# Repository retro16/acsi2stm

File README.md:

ACSI2STM: Atari ST hard drive emulator
======================================

This project is a hard drive emulator for your Atari ST using an inexpensive
STM32 microcontroller and a SD card.

The aim of this project is to be very easy to build, extremely cheap, reliable
and safe for your precious vintage machine. A lot of effort has been put in the
documentation, both for usage and technical aspects.

It can work in 3 ways:

* Mount standard SD/SDHC/SDXC cards on the Atari (FAT16/FAT32/ExFAT).
* Expose raw SD cards as ACSI hard disks connected to the Atari.
* Expose ACSI hard disk image files as hard disks connected to the Atari.

It can also work on STs with broken DMA chips by using the PIO firmware.

It also provides an UltraSatan compatible real-time clock if you add a simple
3V lithium battery such as a CR2032.

Legacy hardware based on Blue Pill designs are supported to various degrees.
[compatibility](doc/compatibility.md) explains which hardware is supported by
this version.

See [RELEASE NOTES](release_notes.md) for details about the current version.

**Final version:** Both software and hardware parts are considered finished, the
project is now mature. Feedback is still welcome and occasional bug fixes may be
released.

Documentation
-------------

The *doc* directory provides documentation for the end-user as well as hardware
implementors or curious people.

This is what you can find:

* [quick_start](doc/quick_start.md): How to setup and upgrade the unit.
* [tutorial](doc/tutorial.md): A tutorial about using hard drives on an Atari ST
  if you never used one before. It will help setting up various hardware
  combinations.
* [standard_configurations](doc/standard_configurations.md): Instructions to
  setup ACSI2STM depending on your hardware and what you want to achieve.
* [tools](doc/tools.md): Documentation for tools provided with ACSI2STM.
* [compatibility](doc/compatibility.md): Information about hardware, firmware
  and software compatibility.
* [troubleshooting](doc/troubleshooting.md): Having problems? Have a look
  here.
* [ordering](doc/ordering.md): A tutorial to order the hardware and flash the
  firmware.
* [gemdrive](doc/gemdrive.md): Technical details about GemDrive. How to mix
  GemDrive with ACSI. How to install GemDrive for EmuTOS.
* [jumpers](doc/jumpers.md): Documents the various jumpers available on the PCB.
* [firmware](doc/firmware.md): Describes the many firmware variants pre-built
  in the release package. Also provides a step-by-step tutorial to compile and
  customize firmware yourself.
* [hardware](doc/hardware.md): How to design and build an ACSI2STM unit
  from scratch (hand wired or your own PCB design).
* [protocols](doc/protocols.md): Technical details about the communication
  protocol between the ACSI2STM unit and the Atari ST.

To people buying/selling hardware
---------------------------------

There are people building and selling products based on this code. This project
is not directly related to any of these people, there is no official hardware
supplier.

Building and selling units is encouraged, as long as the spirit of free software
is preserved and the terms of the license are respected.

The code here is released under the GPLv3 license (see LICENSE file). This has
some implications:

* If you bought a product that contains code based on this project (modified or
  not), you can request the source code to the firmware contained in your
  product. The seller/maker of the product is legally required to provide it.
* If you sell any product based on this code, you **must** provide a link to
  the source.
* If you sell any product based on a modified version of this code, or reusing
  parts of this code, you **must** provide a link to the whole source code of
  the modified version with the product, including any additional
  features/modules you may have added.
* If you redistribute binary versions (modified or not), you **must** provide a
  link to the source code matching exactly the binary you redistribute.
* Any modified version must retain the GPLv3 or a compatible license.
* The name ACSI2STM is not protected. You can reuse it as you wish. Making a
  clear distinction between this code and your product will be greatly
  appreciated (most sellers do).
* The code is provided without warranty, so hardware troubleshooting is best
  effort. If you bought a unit and you have issues, you should contact the
  seller first. Anyway, constructive feedback (including bug reports) is always
  appreciated.
* If a seller refuses to provide the sources, please open a GitHub issue to let
  me know.

**Note**: the Mega STE PCB is copyrighted by Olivier Jan and is released under
the MIT license so it does not have the same restrictions.

If you sell ACSI2STM units, please consider selling the new compact PCB design
instead of custom designs. If the compact design isn't to your taste, please
open a GitHub issue and talk about possible improvements.

Credits
-------

I would like to thank the people that put invaluable information online that
made this project possible in a finite amount of time. Without them, this
project would have not existed. I would also like to thank people giving
feedback, contributing to make the project better.

* Bill Greiman for the SdFat library. It's really fantastic.
* The http://atari.8bitchip.info website and his author, who also contributes
  on various forums.
* The Hatari developpers. I used its source code as a reference for ACSI
  commands, as well as the excellent GEMDOS drive implementation.
* The people who made the FreeMiNT TOS documentation.
* The EmuTOS developers, again the source code is an excellent reference.
* The UltraSatan project for their documentation and their RTC clock tool.
* Uwe Seimet for his SCSI testing tool.
* Jean-Louis Guérin (DrCoolZic) for his excellent "Atari Hard Disk File Systems
  Reference Guide".
* mamejay, Ben Leggett, S0urceror, Sr Antonio, Edu Arana, Frederick321,
  Ulises74, Maciej G., Olivier Gossuin, Marcel Prisi and Tomasz Orczyk for
  their very detailed feedback that helped me a lot for fine tuning the DRQ/ACK
  signals and other various aspects of the projects.
* All people contributing on GitHub, for their code, their ideas, the issues
  they submit, and their patience when things fail !
* Olivier Jan for the Mega STE PCB.
* Tomasz Orczyk for finding a way to have a much better version of GCC and a lot
  of feedback.
* Joe Ceklosky for his feedback and help on fixing RTC issues.
* François Planque for his [extensive explanation about the Mega STE internal drive](https://www.fplanque.com/tech/retro/atari/atari-st-acsi2stm-mega-ste/)
* Diego Parrilla for making the PCB much more reliable.
* Christian Zietz for his expert insight on program loading and Alt-RAM.

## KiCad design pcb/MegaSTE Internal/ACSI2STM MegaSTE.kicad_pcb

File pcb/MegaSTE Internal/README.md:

# ACSI2STM-MSTE
 
This a KiCAD (6.0) design to host an [ACSI2STM](https://github.com/retro16/acsi2stm) directly inside an Atari Mega STE using the internal connector. 
The PCB has been designed to accomodate version 2.x and 3.x of ACSI2STM (aka V2) but also the old V1 design. 
- No external power is required, the 5v is taken directly from the internal ACSI connector, but this has only been tested with a fully recapped PSU. 
- A set of jumper needs to be soldered to configure the board for V1 or V2 as noted on the PCB.

## BOM
- 100 nF Capacitor
- 10uF Radial Capacitor
- Male 2.54 header (Optional)
- 1N5817 Diode 
- Female 2.54 headers
- Amphenol GSD090012SEU SD Card socket
- STM32F103C8T6 "Blue Pill" (original one is highly recommended!!!). 
- Firmware from [ACSI2STM](https://github.com/retro16/acsi2stm)

## Configuration
Configuration is done by simple solder bridges on the pads, instructions are also written on PCB.

### For V1:
- Solder bridge: JP1, JP2, JP3, JP4, JP5, JP6, JP7
- Solder bridge pads 1 and 2 of JP9 (2 leftmost pads)
- Solder bridge pads 1 and 2 of JP10 (2 leftmost pads)

### For V2: 
- Solder bridge pads 2 and 3 of JP9 (2 leftmost pads)
- Solder bridge pads 2 and 3 of JP10 (2 leftmost pads)

### For V3: 
- Solder bridge pads 2 and 3 of JP9 (2 leftmost pads)
- Solder bridge pads 2 and 3 of JP10 (2 leftmost pads)
- Solder bridge JP8 

### Firmware update

A male 3 pin header is optional and only required if you want to program the STM32 without removing it from the Atari.
The RX and TX marking correspond to the STM32 pins A10 an A09, to program the STM32 connect the board's RX to your USB-TTL TX and the board's TX to your USB-TTL-RX:
| USB-TTL | ACSI2STM |
|:---------:|:----------:|
| GND | GND |
| RX | TX |
| TX | RX |

In order to update the STM32:
1. Power-off your MegaSTE
2. Plug the GND, RX and TX to your USB-TTL adapter
3. Move BOOT0 jumper to "1" on the BluePill
3. Plug USB to ACSI2STM
4. Follow the normal update process.
5. Unplug USB, RX, TX and GND
6. Move BOOT0 jumper back to original position
7. Power-on the Mega STE

:warning: Although the diode should avoid USB power from flowing back to the Mega STE, I haven't tested USB plugged-in while the MegaSTE is powered on. :warning:

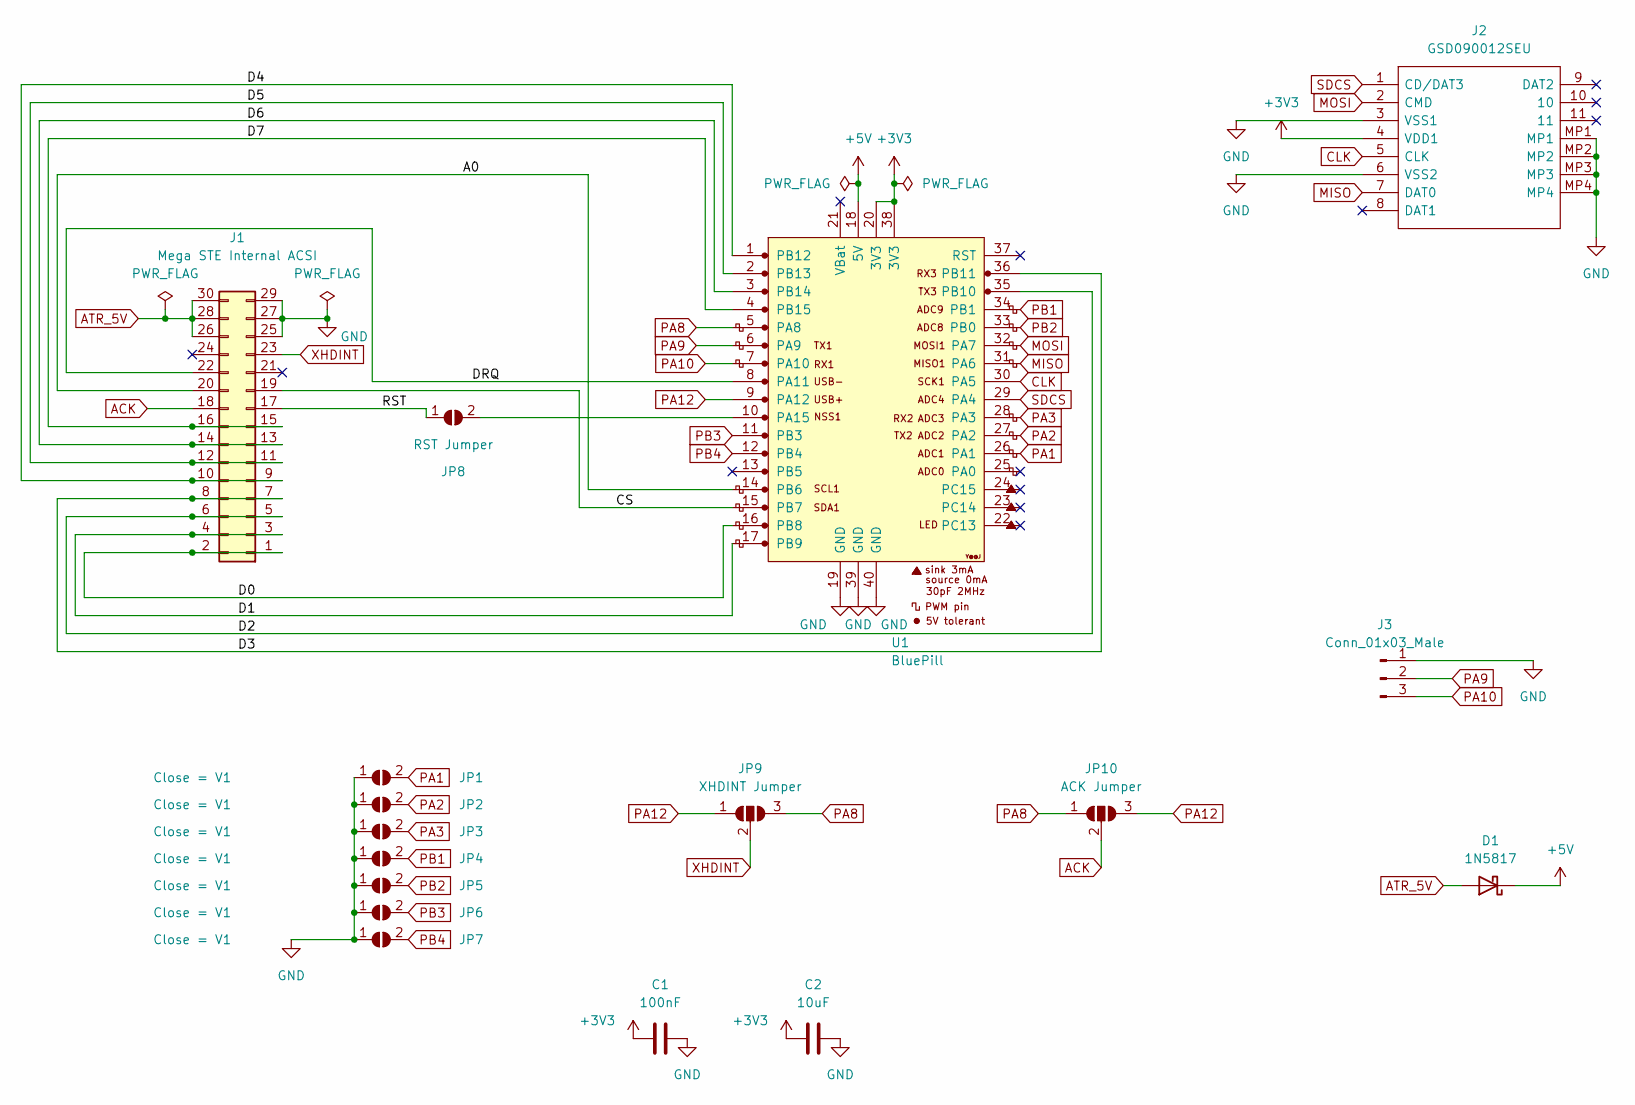
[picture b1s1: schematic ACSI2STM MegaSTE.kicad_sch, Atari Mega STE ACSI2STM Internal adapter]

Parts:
C1: 100nF; C_Disc_D4.3mm_W1.9mm_P5.00mm
C2: 10uF; C_Radial_D5.0mm_H5.0mm_P2.00mm
D1: 1N5817; D_DO-41_SOD81_P10.16mm_Horizontal
J1: Mega STE Internal ACSI; PinSocket_2x15_P2.54mm_Vertical
J2: GSD090012SEU; Mouser Part Number 523-GSD090012SEU
J3: Conn_01x03_Male; PinHeader_1x03_P2.54mm_Vertical
JP1, JP2, JP3, JP4, JP5, JP6, JP7: Close = V1; SolderJumper-2_P1.3mm_Open_Pad1.0x1.5mm
JP8: RST Jumper; SolderJumper-2_P1.3mm_Open_RoundedPad1.0x1.5mm
JP9: XHDINT Jumper; SolderJumper-3_P1.3mm_Open_RoundedPad1.0x1.5mm
JP10: ACK Jumper; SolderJumper-3_P1.3mm_Open_RoundedPad1.0x1.5mm
U1: BluePill; YAAJ_BluePill_1

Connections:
+3V3: C1.1, C2.1, J2.4 (VDD1), U1.20 (3V3), U1.38 (3V3)
+5V: D1.1 (K), U1.18 (5V)
/A0: J1.20, U1.14 (PB6)
/CS: J1.19, U1.15 (PB7)
/D0: J1.1, J1.2, U1.16 (PB8)
/D1: J1.3, J1.4, U1.17 (PB9)
/D2: J1.5, J1.6, U1.35 (PB10)
/D3: J1.7, J1.8, U1.36 (PB11)
/D4: J1.9, J1.10, U1.1 (PB12)
/D5: J1.11, J1.12, U1.2 (PB13)
/D6: J1.13, J1.14, U1.3 (PB14)
/D7: J1.15, J1.16, U1.4 (PB15)
/DRQ: J1.22, U1.8 (PA11)
/RST: J1.17, JP8.1 (A)
ACK: J1.18, JP10.2 (C)
ATR_5V: D1.2 (A), J1.26, J1.28, J1.30
CLK: J2.5 (CLK), U1.30 (PA5)
GND: C1.2, C2.2, J1.25, J1.27, J1.29, J2.3 (VSS1), J2.6 (VSS2), J2.MP1, J2.MP2, J2.MP3, J2.MP4, J3.1, JP1.1 (A), JP2.1 (A), JP3.1 (A), JP4.1 (A), JP5.1 (A), JP6.1 (A), JP7.1 (A), U1.19 (GND), U1.39 (GND), U1.40 (GND)
MISO: J2.7 (DAT0), U1.31 (PA6)
MOSI: J2.2 (CMD), U1.32 (PA7)
unnamed: JP8.2 (B), U1.10 (PA15)
PA1: JP1.2 (B), U1.26 (PA1)
PA2: JP2.2 (B), U1.27 (PA2)
PA3: JP3.2 (B), U1.28 (PA3)
PA8: JP9.3 (B), JP10.1 (A), U1.5 (PA8)
PA9: J3.2, U1.6 (PA9)
PA10: J3.3, U1.7 (PA10)
PA12: JP9.1 (A), JP10.3 (B), U1.9 (PA12)
PB1: JP4.2 (B), U1.34 (PB1)
PB2: JP5.2 (B), U1.33 (PB0)
PB3: JP6.2 (B), U1.11 (PB3)
PB4: JP7.2 (B), U1.12 (PB4)
SDCS: J2.1 (CD/DAT3), U1.29 (PA4)
XHDINT: J1.23, JP9.2 (C)

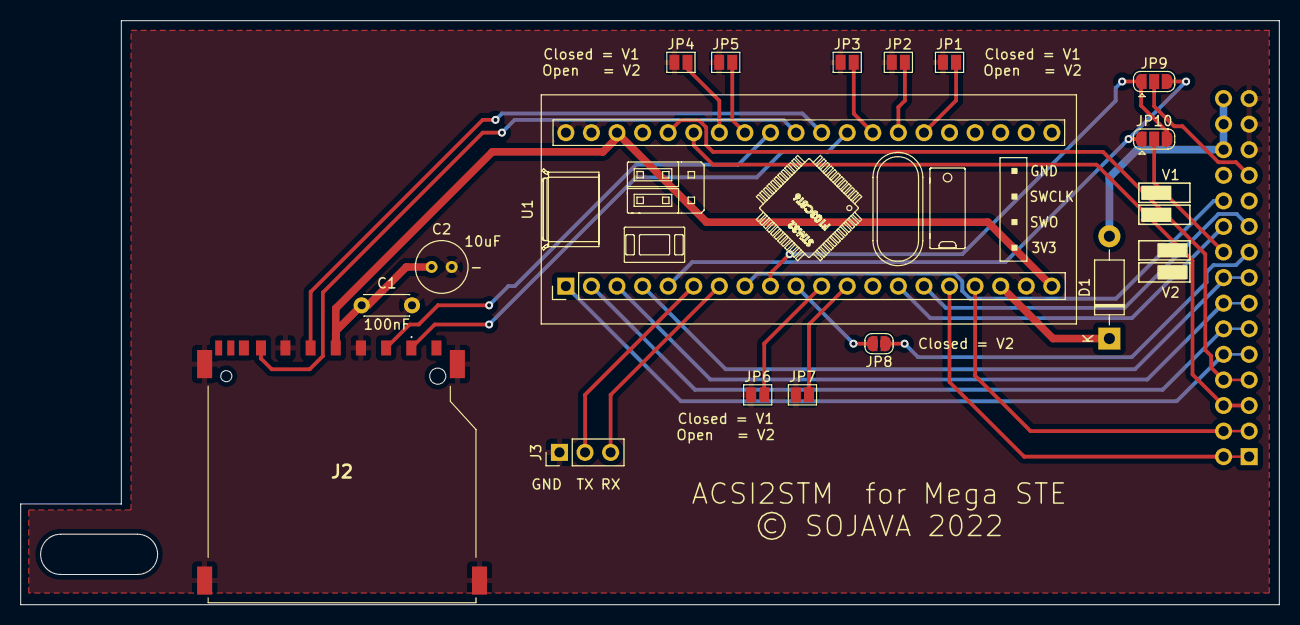
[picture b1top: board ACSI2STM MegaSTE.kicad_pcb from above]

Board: 2 copper layers, 125.0 x 58.0 mm, 17 parts (1 on the bottom side), 34 nets.

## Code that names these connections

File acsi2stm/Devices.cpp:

/* ACSI2STM Atari hard drive emulator
 * Copyright (C) 2019-2025 by Jean-Matthieu Coulon
 *
 * This program is free software: you can redistribute it and/or modify
 * it under the terms of the GNU General Public License as published by
 * the Free Software Foundation, either version 3 of the License, or
 * (at your option) any later version.
 *
 * This program is distributed in the hope that it will be useful,
 * but WITHOUT ANY WARRANTY; without even the implied warranty of
 * MERCHANTABILITY or FITNESS FOR A PARTICULAR PURPOSE.  See the
 * GNU General Public License for more details.
 *
 * You should have received a copy of the GNU General Public License
 * along with the program.  If not, see <http://www.gnu.org/licenses/>.
 */

#include "Devices.h"

#include "Acsi.h"
#include "BlockDev.h"
#include "GemDrive.h"

#include <libmaple/iwdg.h>

// SD slots table, with physical slot ID, SD CS pin and SD write protect pin
SdDev Devices::sdSlots[] = {
  SdDev(0, PA4, PB0),
#if ACSI_SD_CARDS >= 2
  SdDev(1, PA3, PB1),
#endif
#if ACSI_SD_CARDS >= 3
  SdDev(2, PA2, PB3),
#endif
#if ACSI_SD_CARDS >= 4
  SdDev(3, PA1, PB4),
#endif
#if ACSI_SD_CARDS >= 5
  SdDev(4, PA0, PB5),
#endif
};

// ACSI device table
Acsi Devices::acsi[] = {
  Acsi(sdSlots[0]),
#if ACSI_SD_CARDS >= 2
  Acsi(sdSlots[1]),
#endif
#if ACSI_SD_CARDS >= 3
  Acsi(sdSlots[2]),
#endif
#if ACSI_SD_CARDS >= 4
  Acsi(sdSlots[3]),
#endif
#if ACSI_SD_CARDS >= 5
  Acsi(sdSlots[4]),
#endif
};

#if ! ACSI_STRICT
// GemDrive device table
GemDrive Devices::drives[] = {
  GemDrive(sdSlots[0]),
#if ACSI_SD_CARDS >= 2
  GemDrive(sdSlots[1]),
#endif
#if ACSI_SD_CARDS >= 3
  GemDrive(sdSlots[2]),
#endif
#if ACSI_SD_CARDS >= 4
  GemDrive(sdSlots[3]),
#endif
#if ACSI_SD_CARDS >= 5
  GemDrive(sdSlots[4]),
#endif
};
#endif

void Devices::sense() {
#if ACSI_RTC
  FsDateTime::setCallback(getDateTime);
#endif
#if ! ACSI_STRICT && ! ACSI_PIO
  strict = digitalRead(PB2);
#endif

#if ACSI_ID_OFFSET_PINS && ! ACSI_FIRST_ID
  // Check if PA13 is set to VCC
  pinMode(PA13, INPUT_PULLDOWN);
  pinMode(PA14, INPUT);
  delay(1);
  if(digitalRead(PA13)) {
    acsiFirstId = 3;
    goto end;
  }
  pinMode(PA13, INPUT);
  pinMode(PA14, INPUT_PULLUP);
  delay(1);
  if(!digitalRead(PA14)) {
    acsiFirstId = 1;
    goto end;
  }
  pinMode(PA13, OUTPUT);
  digitalWrite(PA13, 0);
  if(!digitalRead(PA14)) {
    acsiFirstId = 2;
  }
end:
  pinMode(PA13, INPUT_PULLUP);
  pinMode(PA14, INPUT_PULLUP);
#endif

#if ! ACSI_STRICT
  GemDrive::closeAll();
#endif
  for(int c = 0; c < sdCount; ++c) {
    sdSlots[c].onReset();
#if ! ACSI_PIO
    acsi[c].onReset();
#endif
  }
}

int Devices::acsiDeviceMask = 0;
#if ! ACSI_STRICT
int Devices::gemDriveMask = 0;
int Devices::gemBootDrive = 8;

void Devices::updateGemBootDrive() {
  for(gemBootDrive = 0; gemBootDrive < 8; ++gemBootDrive)
    if(gemDriveMask & 1 << gemBootDrive)
      return;
}

void Devices::attachGemDrive(int slot) {
  gemDriveMask |= (1 << slot);
  updateGemBootDrive();
}
#endif

void Devices::attachAcsi(int slot) {
  acsiDeviceMask |= (1 << slot);
}

void Devices::detach(int slot) {
  acsiDeviceMask &= ~(1 << slot);
#if ! ACSI_STRICT
  gemDriveMask &= ~(1 << slot);
  updateGemBootDrive();
#endif
}

void Devices::getDateTime(uint16_t *date, uint16_t *time) {
  tm_t now;
  rtc.getTime(now);
  Monitor::verbose(now.year + 1970, '-', now.month, '-', now.day, ' ', now.hour, ':', now.minute, ':', now.second, ' ');
  *date = FS_DATE(now.year + 1970, now.month, now.day);
  *time = FS_TIME(now.hour, now.minute, now.second);
}

void Devices::setDateTime(uint16_t date, uint16_t time) {
  tm_t newDateTime;
  newDateTime.year = FS_YEAR(date) - 1970;
  newDateTime.month = FS_MONTH(date);
  newDateTime.day = FS_DAY(date);
  newDateTime.hour = FS_HOUR(time);
  newDateTime.minute = FS_MINUTE(time);
  newDateTime.second = FS_SECOND(time);

  Monitor::verbose("Setting date to ");
  rtc.setTime(newDateTime);
  Monitor::verbose(newDateTime.year + 1970, '-', newDateTime.month, '-', newDateTime.day, ' ', newDateTime.hour, ':', newDateTime.minute, ':', newDateTime.second, ' ');
}

bool Devices::isDateTimeSet() {
  tm_t now;
  rtc.getTime(now);
  return now.year > 1980 - 1970 && now.year < 2107 - 1970;
}

#if ! ACSI_STRICT
bool Devices::strict = false;
#endif
#if ACSI_ID_OFFSET_PINS
int Devices::acsiFirstId = ACSI_FIRST_ID;
#endif

uint8_t Devices::buf[ACSI_BLOCKSIZE * ACSI_BLOCKS];
RTClock Devices::rtc(RTCSEL_LSE);

int Devices::computeChecksum(uint8_t *block) {
  int checksum = 0;
  for(int i = 0; i < ACSI_BLOCKSIZE; i += 2)
    checksum += ((int)block[i] << 8) + (block[i+1]);

  return checksum & 0xffff;
}

void Devices::blocksToString(uint32_t blocks, char *target) {
  // Characters: 0123
  //            "213G"

  uint32_t sz = (blocks + 1) / 2;
  target[3] = 'K';
  if(sz > 999) {
    sz = (sz + 1023) / 1024;
    target[3] = 'M';
  }
  if(sz > 999) {
    sz = (sz + 1023) / 1024;
    target[3] = 'G';
  }
  if(sz > 999) {
    sz = (sz + 1023) / 1024;
    target[3] = 'T';
  }

  // Roll our own int->string conversion.
  // Libraries that do this are surprisingly large.
  for(int i = 2; i >= 0; --i) {
    if(sz || i == 2)
      target[i] = '0' + sz % 10;
    else
      target[i] = ' ';
    sz /= 10;
  }
}

// vim: ts=2 sw=2 sts=2 et

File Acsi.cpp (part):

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 * along with the program.  If not, see <http://www.gnu.org/licenses/>.
 */

#define A1 PB6 // Must be on port B
#define CS PB7 // Must be on port B
#define IRQ PA8
#define DRQ PA11 // Must be on Timer1 channel output
#define ACK PA12 // Must be on Timer1 external clock
// Data pins are on PC8-PB15

// Pin masks for direct port access
#define A1_MASK  0b0000000001000000
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these signals. Data flow:
             __________
         CLK|          |CH4
  ACK ----->|  Timer1  |-----> PA11 (DRQ)
            |          |
            |          |CH3
            |          |------------
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                     |_______|   |______|   |__________|

 * ACK is used as Timer1 clock.
 * PA11 (DRQ) is used as a PWM output that goes up whenever Timer1 receives a clock tick.
 * Timer1 triggers a STM32 DMA transfer whenever Timer1 receives a clock tick.
 * The STM32 DMA engine copies GPIOB to Timer1 CH1 compare value.
 * Timer1 CH1 is used as a simple buffer because GPIOB is considered as memory
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
DMA block transfer stop process:

 * Set DRQ pin as input
 * Disable Timer1


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
DMA block transfer stop process:

 * Set DRQ pin as input
 * Disable Timer1

*/
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}

void Acsi::releaseRq() {
  GPIOA->regs->CRH = 0x44444BB4; // Set ACK, IRQ and DRQ as inputs
}

void Acsi::releaseDataBus() {
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
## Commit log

2019-02-23 First commit.
2019-02-23 Refactoring
2019-02-23 More code cleaning
2019-02-23 Pushed on github
2019-02-23 Added GPLv3 header to the code.
2019-02-23 Added documentation about programming the chip.
2019-02-23 Minor code rework
2019-02-24 Implemented a lot of the extended commands. Inspired from the Hatari emulator code.
2019-02-24 A bit of cleanup
2019-03-07 Tentative for Multi SD card
2019-03-09 Multi SD card works OK
2019-03-09 Updated doc
2019-03-09 Better explanation for SD wiring
2021-01-28 Added feedback about write issues.
2021-02-08 Improved README thanks to user feedback.
2021-04-23 ACSI2STM v2.0 beta. Solves timing issues and improves stability a lot.
2021-04-29 Ported to the newer SdFat library (removed shipped Sd2CardX). Small bug fixes and adjustments.
2021-05-02 Version 2.0
    Complete code refactor.
    Fixed timing problems.
    Fixed protocol issues.
    Better verbose output.
    Added support for disk images.
2021-05-02 Fix checksum (fixes the bootable flag)
2021-05-03 Split debug functions to their own file. Cleaner logs.
2021-05-03 Corrected debug log
2021-05-04 Removed logs between commandSuccess and waitCommand as this may cause command skip in debug mode.
2021-05-08 (testing) delay DMA sampling on DMA reads.
2021-05-15 Made DMA sample delay optional as this doesn't always improve things.
2021-07-29 Use a hardware timer for CS and A1 pulses. Added optional hardware filters for ACK and CS signals.
2022-03-01 v2.2: Slower DMA and SD for better compatibility. Updated README.
2022-03-14 Improved SCSI compatibility
2022-03-19 2.3 beta. Code refactoring. Updated README and debug_output.
2022-03-20 2.3 beta 2. Watchdog activated, proper removable media support, cleaner error handling.
2022-03-20 2.3d: Added real-time clock. More documentation.
2022-03-20 2.30 stable. Finally !
2022-03-21 2.31: Slowed down ACSI bus wait to accomodate for slower chips. Shorter watchdog. Fixed version in the user manual.
2022-03-23 2.4a: self-test tool, pins changed, strict mode, many bug fixes
2022-03-25 Stability improvements for STM32 clones. Split nosdcard and acsitest.
2022-03-26 2.4c:More command tests,tiny fixes
2022-03-26 2.32:Added build_asm.sh. Backported PB3/PB4 fix from 2.4.
2022-03-26 Added build_asm.sh
2022-03-26 2.40:Log cleanup. Tests proved that ACSI_CS_FILTER is no good.
2022-04-04 2.41: Fixed command handling in write mode.
2022-04-05 2.41: [NOT] Fixed command handling in write mode. Does not work.
2022-04-05 2.42: Fix CS for real.
2022-04-07 3.0a: Integrated driver. Added RESET signal. Redone DMA port logic.
2022-04-09 2.43: ACSI_ACK_FILTER only on STM32->ST transfers
2022-04-09 3.0b: Still imperfect driver.
2022-04-12 2.44: Added a compile-time option to invert SD card write lock.
2022-04-15 3.0c: Print partitions. Bug fixes. Added ACSI_SD_WRITE_LOCK define.
2022-04-19 3.0d: A lot of new features, refactored tools and build
2022-04-21 3.0e: Better hotswap and error handling
2022-04-30 3.0f: Tools are barely working
2022-05-15 3.0g: Work on tools, fixed driver bug.
2022-05-16 3.0h: Replaced broken watchdog by a simple timeout timer.
2022-06-26 3.00: With an official driver and PCB
2022-06-28 3.01: Improved documentation
2022-08-04 Added PCB for MegaSTE internal connector
2022-09-03 Minor fix when compiling asm without setup. Minor doc update.
2022-09-07 Add boot drive selection to the driver. Add basic sanity checks in release build script. Bumped to 3.1
2022-09-08 Cosmetic fixes in a2setup. Require bash for shell scripts.
2022-09-09 Allow remapping C: to A:. Overlay is now only on first SD slot. Removed useless remote code execution. Build scripts improvements, now work out of source.
2022-09-09 Remaps C: to A: successfully
2022-09-09 Added surface test and continuous test modes. Need to optimize size.
2022-09-10 FAT16 formating is now Windows compatible. Improved a2stboot FAT/MBR autodetection.
2022-09-10 Size optimizations. Cosmetic changes.
2022-09-13 Update README.md
    Included link to Troubleshooting from README.md
2022-09-18 Documentation changes
2022-09-18 Added a delay between command and DMA transfers. Version bump.
2022-09-18 Fixed getbpb and rwabs low-level calls.
2022-09-18 Bootloader is now windows-compatible. Added a better guide for EmuTOS installation.
2022-09-18 Fixed rwabs physical mode
2022-09-18 Added EmuTOS boot support. Fixed rwabs physical mode.
2022-09-18 Last minute fix for boot overlay slot limit
2023-04-12 4.0a initial commit. Still not good enough for a release though.
2023-04-12 Added things to do before alpha release.
2023-04-12 Fully reworked hotplug / media check logic. Cleaned all warnings. Added dynamic drive letter.
2023-04-13 Working on hot swap stabilization
2023-04-13 Fixed reset detection (STM32 timers are really broken). Some work here and there.
2023-04-15 4.0b: Fixed most GemDrive issues, especially Pexec.
2023-04-15 Renamed release package (fixes #39)
2023-04-30 4.0c: Needs more bug fixes
2023-05-18 4.0d: ACSI tests okay. More SCSI fixes.
2023-05-21 4.0e: Added A1 workaround. Fixed disk image support. ACSI mode is final. Much progress in GemDrive mode.
2023-05-22 4.0f: Added firmware flashing support.
2023-06-03 4.0f: Release candidate for 4.00
2023-06-04 Removed LONG access to DMA in syshook init. Simplified mediaId management. Removed dead code for useless FD cache.
2023-06-04 Safer SD card init (but slower). Debug log cleanup.
2023-06-04 Fixed Dgetpath on root directory of a swapped drive.
2023-06-04 4.00: A giant leap for ST-kind
2023-06-05 4.01: Small fixes in GemDrive and more tests
2023-06-06 4.10: Clock support and unicode for GemDrive
2023-07-14 Added Compact PCB. Blind fix for RTC.
2023-07-14 Doc improvements.
2023-07-16 4.2a: Need to test compact PCB.
2023-07-16 Added EmuTOS loader. More documentation updates.
2023-07-17 Work on the documentation
2023-07-17 Added 2-phase init. Reduced some logging to optimize space.
2023-07-17 4.2b: EmuTOS, boot sector fix, documentation update.
2023-07-18 4.11: Clock fix
2023-07-25 Small doc adjustments
2023-07-25 Commented microprograms
2023-08-12 Updated PCB (new version untested). Added 3D printed enclosure. Doc updates again. Still has a date bug.
2023-08-12 Fixed date handling. Version bump.
2023-08-12 4.12: Fix months between august and december.
2023-08-12 Added better oscilloscope traces in documentation.
2023-08-24 5.0a: Big rework for 5.00
2024-10-02 ACSI2STM compact custom version
2024-10-25 5.0b: Release candidate for final version
2024-10-26 TT-RAM support,copyright bump,small fixes
2024-10-26 Fixed bugs, speed optimization, 64k verbose firmware
2024-10-27 Fixed mediaId cache
2024-10-27 5.0c: Refinements and minor fixes
2024-10-27 Added doc for tools. Removed useless files. Fixed tools text headers.
2024-10-29 Removed (obsolete) full-featured PCB. Doc fixes.
2024-10-29 5.0d: PIO mode. Various bug fixes.
2024-10-30 More documentation work
2024-10-30 Fix overrun in BSS memory clear
2024-11-02 Minor ASM rework
2024-11-02 5.0e: Fixed GemDrive boot. Removed some verbose logs to fit firmware in 64k.
2024-11-03 Added the much needed tutorial to documentation
2024-11-08 Added multi device support for GEMDRIVE.PRG
2024-11-08 Fixed HDDFLASH
2024-11-08 Fixed GemDrive boot
2024-11-08 Minor fixes in GemDrive boot. Minor doc fixes.
2024-11-08 5.0f: Lots of refinements
2024-11-09 Fixed a weird bug when using multiple ACSI2STM units. Doc updates.
2024-11-09 Improved ACSI perf when no SD. GemDrive init fix. Doc fix.
2024-11-10 Fix fast IRQ. Fix CS timeout. Adjust doc.
2024-11-10 5.0g: IRQ / CS stability fixes. Multi unit improvements.
2024-11-10 Bump VERSION to 5.00
2024-11-10 More minor documentation fixes
2024-11-10 Generate a TOS compatible HD image. Improved content.
2024-11-11 Release notes update
2024-11-11 Reinitialize SD cards at GemDrive boot. Debug output cleanup.
2024-11-11 5.00: Professionally assembled PCB, EmuTOS, PIO mode, multiple devices and fixes
2024-11-30 Correctly set internal ST clock in GemDrive mode. Size optimizations to fit 64k.
2024-11-30 Removed Tgetdate/time hooks and let the ST handle its own clock.
2024-12-04 5.0i: Date fix
2025-01-14 5.1a: Super Compact PCB, hardware revision, date set fix
2025-01-23 Super Compact PCB, Compact PCB revision 1.1
2025-01-25 5.1b: Added Dockerfile, updated doc, updated copyright date
2025-02-11 New MegaSTE internal board, base on compact version.
2025-02-12 Remove Logo Fix some capacitors
2025-05-18 skip gemdrive mode if any modifier key (shift/ctrl/alt) is pressed at boot time
2025-05-18 prevent macos on arm machines from pulling an arm debian (that has some needed tools missing compared to the amd64 variant)
2025-06-14 -changed mediaIds from uint32_t to uin16_t, making space for safe storage of the attribute filter param; this was using the last byte of d_fname[14] before, which meant it could be overwritten by sof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
2026-06-03 Implement Fxattr (op $12C) to fix MiNTLib open() on GemDrive

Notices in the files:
Acsi.cpp:
Copyright (C) 2019-2021 by Jean-Matthieu Coulon
This Library is free software: you can redistribute it and/or modify
pcb/MegaSTE Internal/ACSI2STM MegaSTE.kicad_pcb:
© SOJAVA 2022
